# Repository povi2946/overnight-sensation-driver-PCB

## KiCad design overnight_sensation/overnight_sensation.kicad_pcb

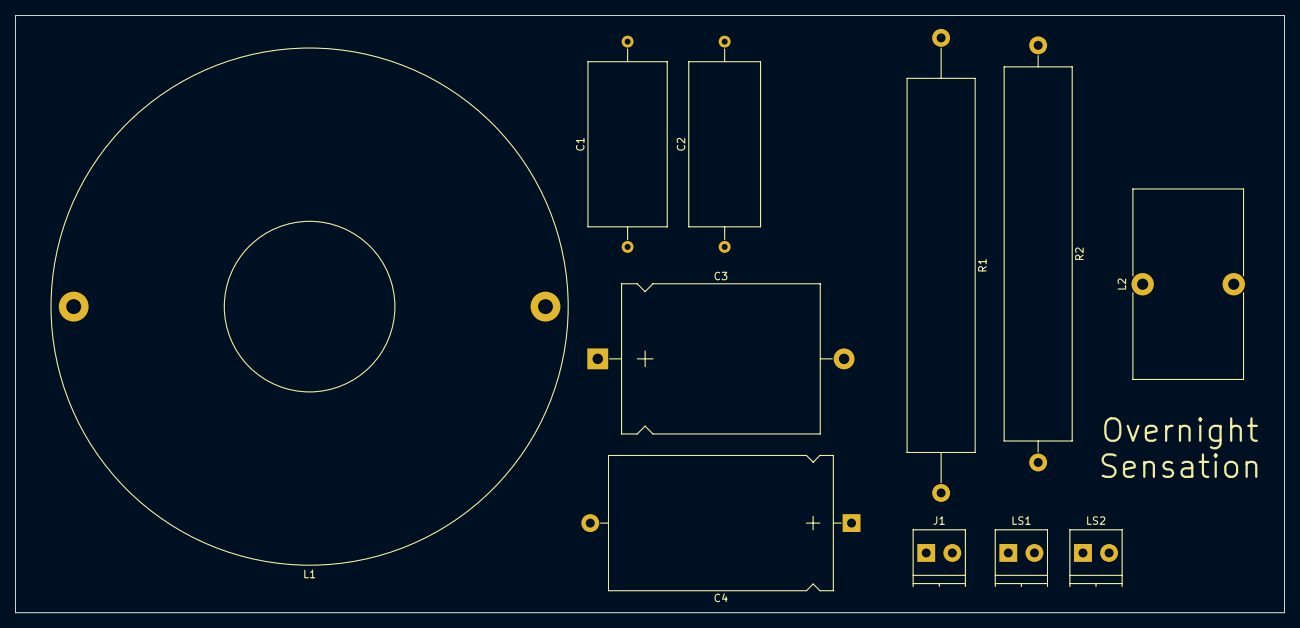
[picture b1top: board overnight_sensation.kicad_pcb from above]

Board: 2 copper layers, 170.0 x 80.0 mm, 11 parts (0 on the bottom side), 6 nets, no tracks yet.

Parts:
C1: 1.5uF; C_Axial_L22.0mm_D10.5mm_P27.50mm_Horizontal
C2: 0.22uF; C_Axial_L22.0mm_D9.5mm_P27.50mm_Horizontal
C3: 2.2uF; CP_Axial_L26.5mm_D20.0mm_P33.00mm_Horizontal
C4: 6.8uF; CP_Axial_L30.0mm_D18.0mm_P35.00mm_Horizontal
J1: Screw_Terminal_1x02; TerminalBlock_Pheonix_PT-3.5mm_2pol
L1: 1.1mH; L_Toroid_Horizontal_D69.1mm_P63.20mm_Vishay_TJ9
L2: 0.35mH; L_Toroid_Vertical_L25.4mm_W14.7mm_P12.20mm_Vishay_TJ5_BigPa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
LS1: HIVI B4N; TerminalBlock_Pheonix_PT-3.5mm_2pol
LS2: Daytona ND20FA; TerminalBlock_Pheonix_PT-3.5mm_2pol
R1: 60R; R_Axial_Power_L50.0mm_W9.0mm_P60.96mm
R2: 10R; R_Axial_Power_L50.0mm_W9.0mm_P55.88mm

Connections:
/BLACK_1: C4.2, J1.2, L2.2, LS1.2, LS2.2, R2.2
/RED_1: C1.2, C2.2, J1.1, L1.2
unnamed: C1.1, C3.2, L2.1
unnamed: C2.1, C4.1, L1.1, LS1.1
unnamed: C3.1, R1.2
unnamed: LS2.1, R1.1, R2.1

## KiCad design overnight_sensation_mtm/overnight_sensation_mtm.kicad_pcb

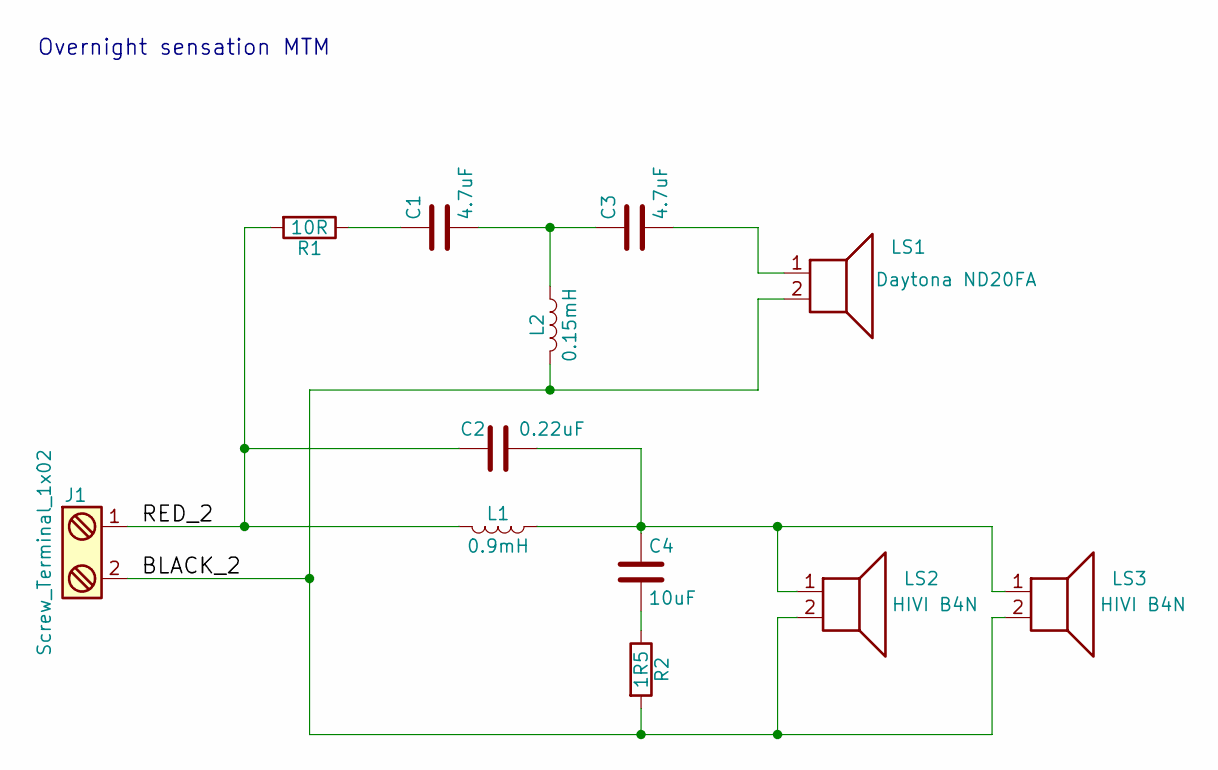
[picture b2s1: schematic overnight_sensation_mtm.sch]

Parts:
C1, C3: 4.7uF; CP_Axial_L29.0mm_D16.0mm_P35.00mm_Horizontal
C2: 0.22uF; C_Axial_L22.0mm_D9.5mm_P27.50mm_Horizontal
C4: 10uF; CP_Axial_L34.5mm_D20.0mm_P41.00mm_Horizontal
J1: Screw_Terminal_1x02; TerminalBlock_Pheonix_PT-3.5mm_2pol
L1: 0.9mH; L_Toroid_Horizontal_D49.3mm_P44.60mm_Vishay_TJ8
L2: 0.15mH; L_Toroid_Vertical_L28.6mm_W14.3mm_P11.43mm_Bourns_5700
LS1: Daytona ND20FA; TerminalBlock_Pheonix_PT-3.5mm_2pol
LS2, LS3: HIVI B4N; TerminalBlock_Pheonix_PT-3.5mm_2pol
R1: 10R; R_Axial_Power_L50.0mm_W9.0mm_P55.88mm
R2: 1R5; R_Axial_Power_L50.0mm_W9.0mm_P60.96mm

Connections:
/BLACK_2: J1.2, L2.2, LS1.2, LS2.2, LS3.2, R2.2
/RED_2: C2.2, J1.1, L1.2, R1.2
unnamed: C1.1, R1.1
unnamed: C1.2, C3.1, L2.1
unnamed: C2.1, C4.1, L1.1, LS2.1, LS3.1
unnamed: C3.2, LS1.1
unnamed: C4.2, R2.1

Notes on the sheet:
Overnight sensation MTM

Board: 2 copper layers, 12 parts (0 on the bottom side), 7 nets, no tracks yet.

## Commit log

2017-05-27 Added old files
2017-06-16 added old schematic
